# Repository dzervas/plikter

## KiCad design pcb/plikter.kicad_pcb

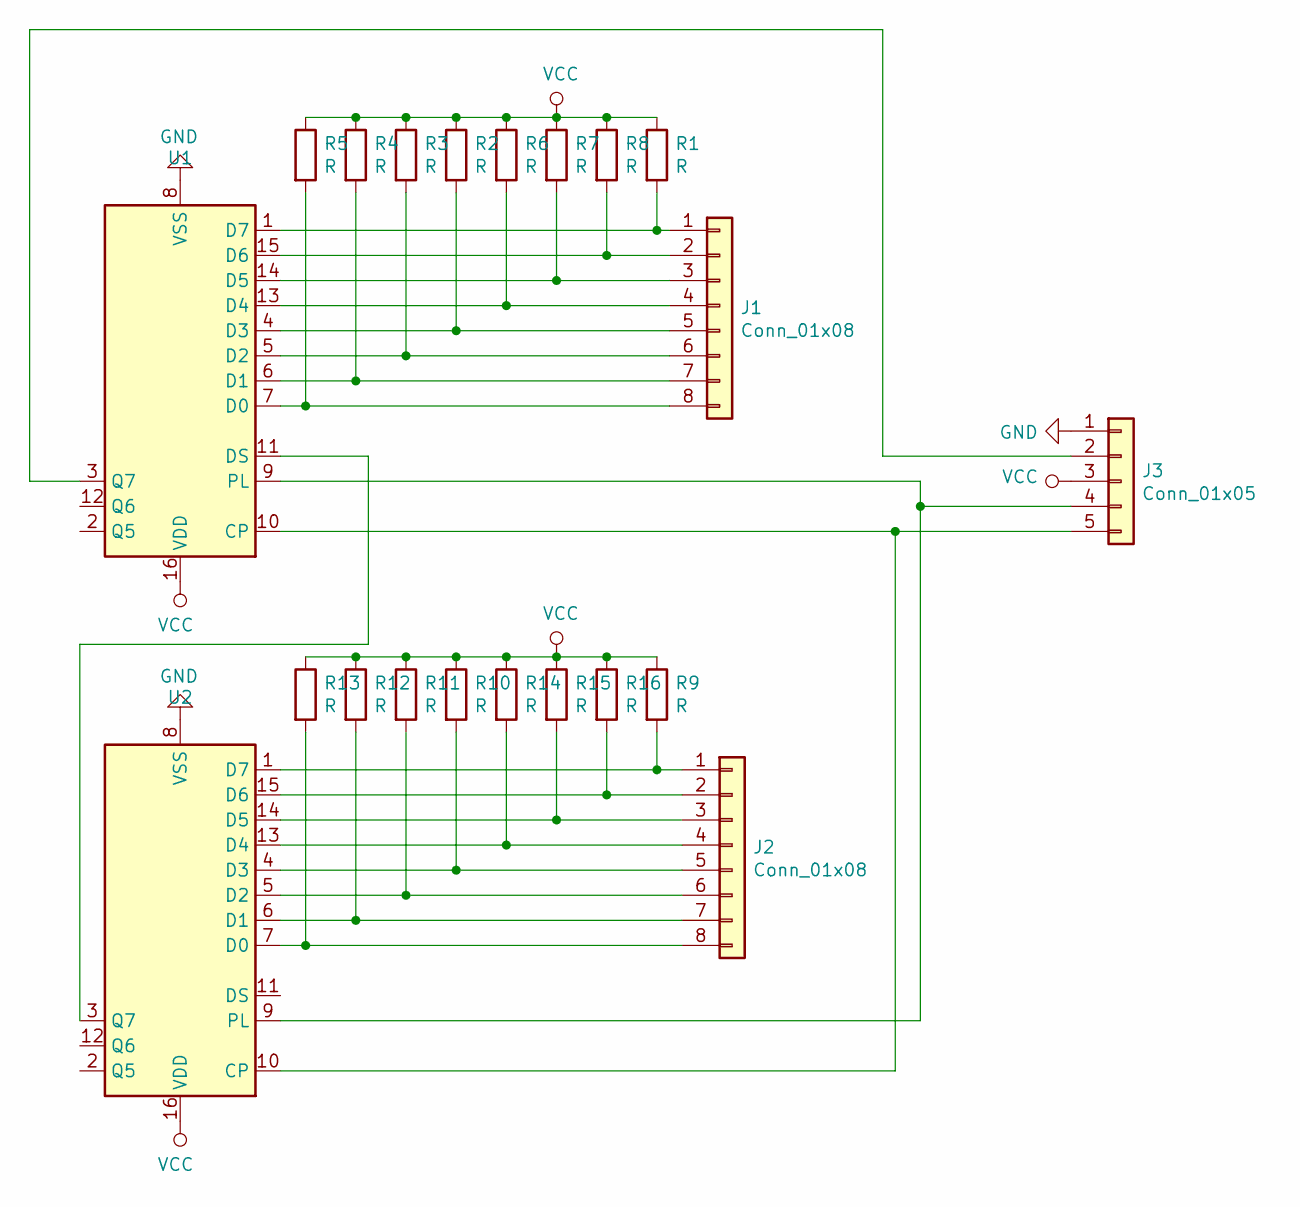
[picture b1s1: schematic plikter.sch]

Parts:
J1, J2: Conn_01x08
J3: Conn_01x05; PinHeader_1x05_P2.54mm_Vertical
R1, R2, R3, R4, R5, R6, R7, R8, R9, R10, R11, R12, R13, R14, R15, R16: R; R_0805_2012Metric
U1, U2: 4021; DIP-16_W7.62mm_LongPads

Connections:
GND: J3.1, U1.8 (VSS), U2.8 (VSS)
unnamed: J1.1, R1.2, U1.1 (D7)
unnamed: J1.2, R8.2, U1.15 (D6)
unnamed: J1.3, R7.2, U1.14 (D5)
unnamed: J1.4, R6.2, U1.13 (D4)
unnamed: J1.5, R2.2, U1.4 (D3)
unnamed: J1.6, R3.2, U1.5 (D2)
unnamed: J1.7, R4.2, U1.6 (D1)
unnamed: J1.8, R5.2, U1.7 (D0)
unnamed: J2.1, R9.2, U2.1 (D7)
unnamed: J2.2, R16.2, U2.15 (D6)
unnamed: J2.3, R15.2, U2.14 (D5)
unnamed: J2.4, R14.2, U2.13 (D4)
unnamed: J2.5, R10.2, U2.4 (D3)
unnamed: J2.6, R11.2, U2.5 (D2)
unnamed: J2.7, R12.2, U2.6 (D1)
unnamed: J2.8, R13.2, U2.7 (D0)
unnamed: J3.2, U1.3 (Q7)
unnamed: J3.4, U1.9 (PL), U2.9 (PL)
unnamed: J3.5, U1.10 (CP), U2.10 (CP)
unnamed: U1.11 (DS), U2.3 (Q7)
VCC: J3.3, R1.1, R2.1, R3.1, R4.1, R5.1, R6.1, R7.1, R8.1, R9.1, R10.1, R11.1, R12.1, R13.1, R14.1, R15.1, R16.1, U1.16 (VDD), U2.16 (VDD)

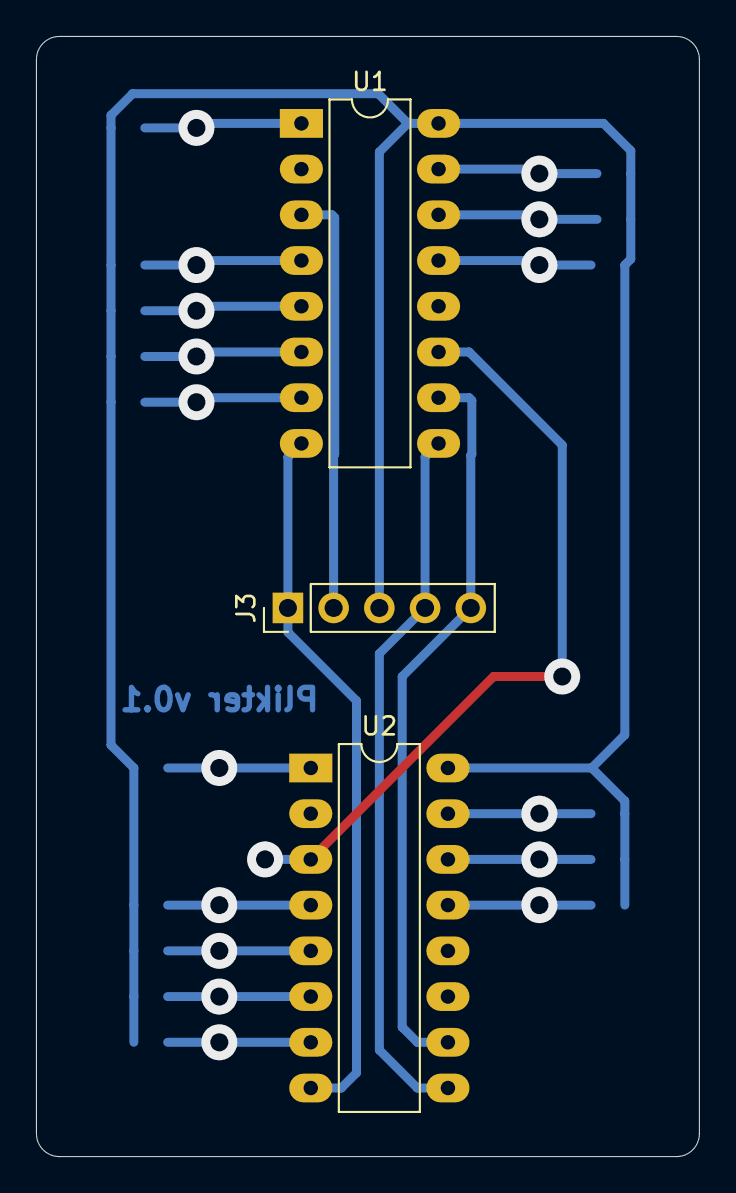
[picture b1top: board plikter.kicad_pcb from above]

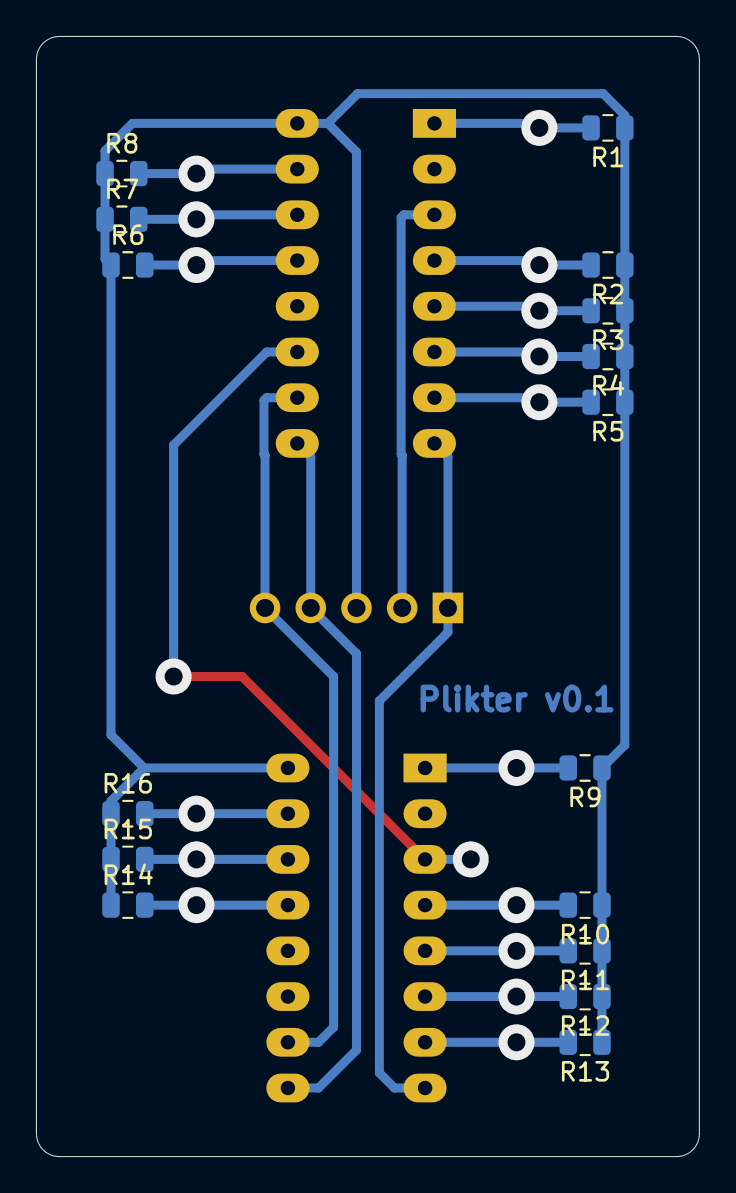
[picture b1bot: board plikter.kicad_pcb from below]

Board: 2 copper layers, 36.8 x 62.2 mm, 19 parts (16 on the bottom side), 22 nets.

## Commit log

2020-04-25 Name changes
2020-04-25 Add temporary display support
2020-04-25 Make screen feature optional
2020-04-26 Use my branch of the Keypad library
2020-04-27 Add shift register breakout board sources
2020-04-28 Move traces to the back
2020-04-28 Move pcb files to correct folder
2020-05-12 Board changes
2020-05-15 Corrected the keyboard map & added second keymap on FN key pressed
2020-05-15 Remove screen code
2020-05-15 Add battery reporting - resolves #4
2020-05-18 Fix Fn key handling
2020-05-18 Define the Fn key
2020-05-19 Fix some bt connection bugs
2020-05-19 Use timers instead of loop
2020-05-22 Add battery advertising service
2020-05-25 Add multi connection support
2020-05-27 Change clearBonds shortcut to Fn + Del 4 times
2020-05-27 Add kindof mutexes to concurrent functions
2020-05-27 Keep advertising after disconnect
2020-05-28 Major optimization - 42ms latency average
2020-05-28 Code cleanup
2020-05-29 Remove travis file
2020-06-25 Latency droped a lot - to ~10ms mostly
2020-06-30 Minor switch case rearrange
2020-06-30 Add Rust boilerplate - ready to start implementation
2020-08-14 Slower matrix scanning - better key accuracy
2020-08-25 Try to make everything work together
2020-09-08 Implement input report buffering - send HID keyboard reports in batches
2020-09-08 Remove useless folders & ramp up debouncing to 20ms (too high?)
2020-09-15 Guard debug output with the debug flag CFG_DEBUG
2020-09-15 Remove mutexes. This is a single core MCU, FFS
